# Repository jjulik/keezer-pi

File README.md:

# keezer-pi
Client/Server code for building a Keezer with a Raspberry Pi

## Complete setup guide
Download the raspbian lite image and put it on a micro SD card.

### Configure keyboard (and enable SSH)
`sudo raspi-config`

### Set the machine name
`sudo vi /etc/hosts`
`sudo vi /etc/hostname`

### Backup your wpa_supplicant
`sudo cp /etc/wpa_supplicant/wpa_supplicant.conf ~/wpa_supplicant.conf.bac`

### Connect to Wi-Fi
`wpa_passphrase "network_name" "passphrase" | sudo tee -a /etc/wpa_supplicant/wpa_supplicant.conf > /dev/null`

Then go edit the wpa_supplicant.conf to not have the password

`wpa_cli -i wlan0 reconfigure`

Check with

`ifconfig wlan0`

### Configure Wi-Fi to connect on boot
Set interface wlan0 in dhcpcd.conf

### Update Pi
`sudo apt-get update`
`sudo apt-get upgrade`

### Enable 1 wire interface
Edit /boot/config.txt

Add dtoverlay=w1-gpio

Then reboot the pi

`sudo shutdown -r -t 0`

### Install vim, git, and pip
`sudo apt-get install vim, git, pip`

### Clone the repo
`git clone https://github.com/jjulik/keezer-pi.git`

### Configure keezer-pi
Copy the keezer-pi.config.example to keezer-pi.config

Then edit the settings

### Install keezer-pi
`sudo ./install.sh`

Reboot the pi once more

`sudo shutdown -r -t 0`

And everything should be working correctly now

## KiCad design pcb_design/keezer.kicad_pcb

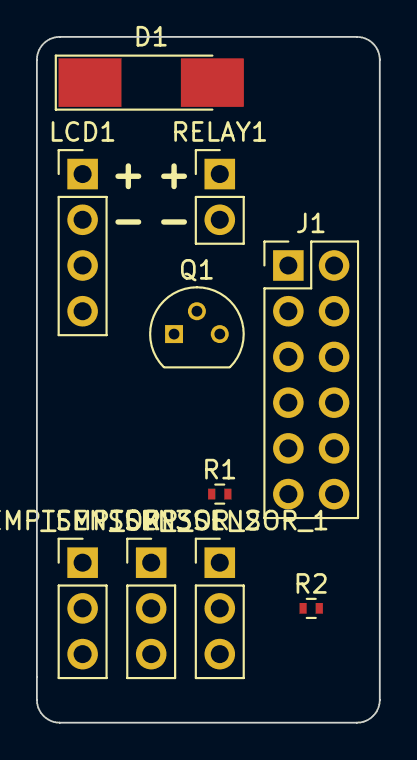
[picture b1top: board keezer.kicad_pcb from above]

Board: 2 copper layers, 19.1 x 38.1 mm, 10 parts (0 on the bottom side), 9 nets, no tracks yet.

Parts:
D1: D; D_MELF_Handsoldering
J1: CONN_02X06; Pin_Header_Straight_2x06_Pitch2.54mm
LCD1: CONN_01X04_FEMALE; Socket_Strip_Straight_1x04_Pitch2.54mm
Q1: PN2222A; TO-92_Molded_Narrow
R1: 1K; R_0402
R2: 3.9K; R_0402
RELAY1: CONN_01X02_FEMALE; Socket_Strip_Straight_1x02_Pitch2.54mm
TEMP_SENSOR_1, TEMP_SENSOR_2, TEMP_SENSOR_3: CONN_01X03_FEMALE; Socket_Strip_Straight_1x03_Pitch2.54mm

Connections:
+3V3: J1.2, R2.1, TEMP_SENSOR_1.1, TEMP_SENSOR_2.1, TEMP_SENSOR_3.1
+5V: D1.1, J1.1, LCD1.1, RELAY1.1
BCM4: J1.8, R2.2, TEMP_SENSOR_1.3, TEMP_SENSOR_2.3, TEMP_SENSOR_3.3
BCM17: J1.12, R1.1
GND: J1.10, LCD1.2, Q1.1, TEMP_SENSOR_1.2, TEMP_SENSOR_2.2, TEMP_SENSOR_3.2
RELAY_OUT: D1.2, Q1.3, RELAY1.2
SCL: J1.6, LCD1.3
SDA: J1.4, LCD1.4
TRANSISTOR_BASE: Q1.2, R1.2

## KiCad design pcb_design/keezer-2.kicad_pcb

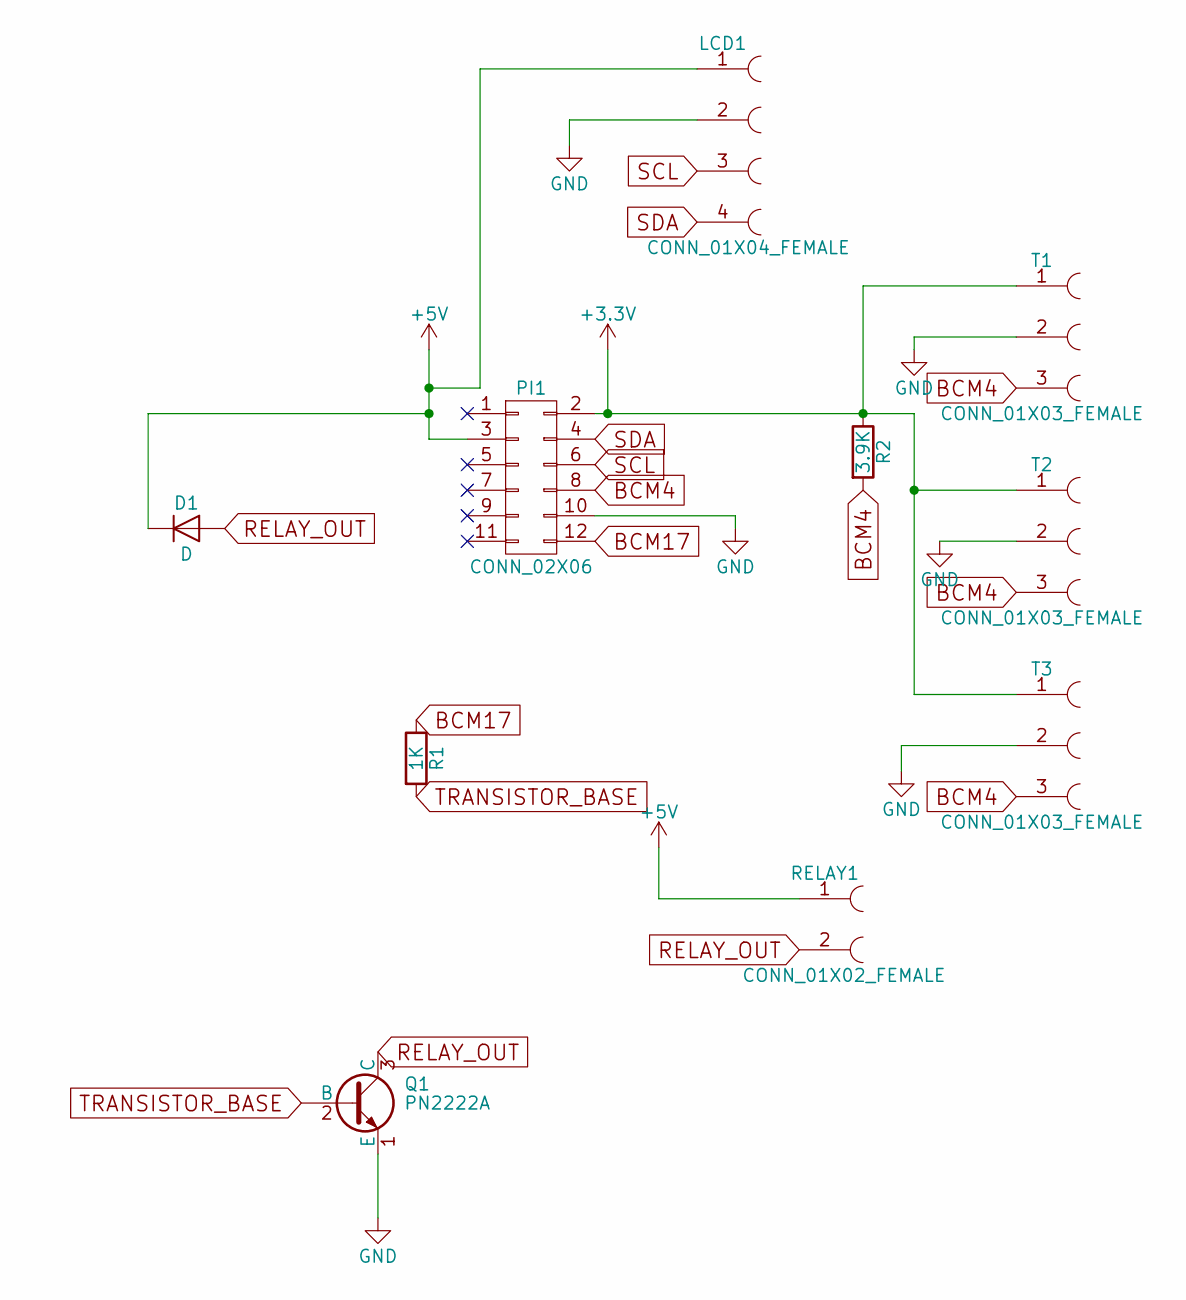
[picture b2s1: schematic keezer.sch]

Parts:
D1: D; D_DO-41_SOD81_P7.62mm_Horizontal
LCD1: CONN_01X04_FEMALE; Socket_Strip_Angled_1x04_Pitch2.54mm
PI1: CONN_02X06; Pin_Header_Straight_2x06_Pitch2.54mm
Q1: PN2222A; TO-92_Inline_Wide
R1: 1K; R_Axial_DIN0207_L6.3mm_D2.5mm_P7.62mm_Horizontal
R2: 3.9K; R_Axial_DIN0207_L6.3mm_D2.5mm_P7.62mm_Horizontal
RELAY1: CONN_01X02_FEMALE; Socket_Strip_Angled_1x02_Pitch2.54mm
T1, T2, T3: CONN_01X03_FEMALE; Socket_Strip_Angled_1x03_Pitch2.54mm

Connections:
+3V3: PI1.2, R2.1, T1.1, T2.1, T3.1
+5V: D1.1 (K), LCD1.1, PI1.3, RELAY1.1
BCM4: PI1.8, R2.2, T1.3, T2.3, T3.3
BCM17: PI1.12, R1.1
GND: LCD1.2, PI1.10, Q1.1 (E), T1.2, T2.2, T3.2
RELAY_OUT: D1.2 (A), Q1.3 (C), RELAY1.2
SCL: LCD1.3, PI1.6
SDA: LCD1.4, PI1.4
TRANSISTOR_BASE: Q1.2 (B), R1.2

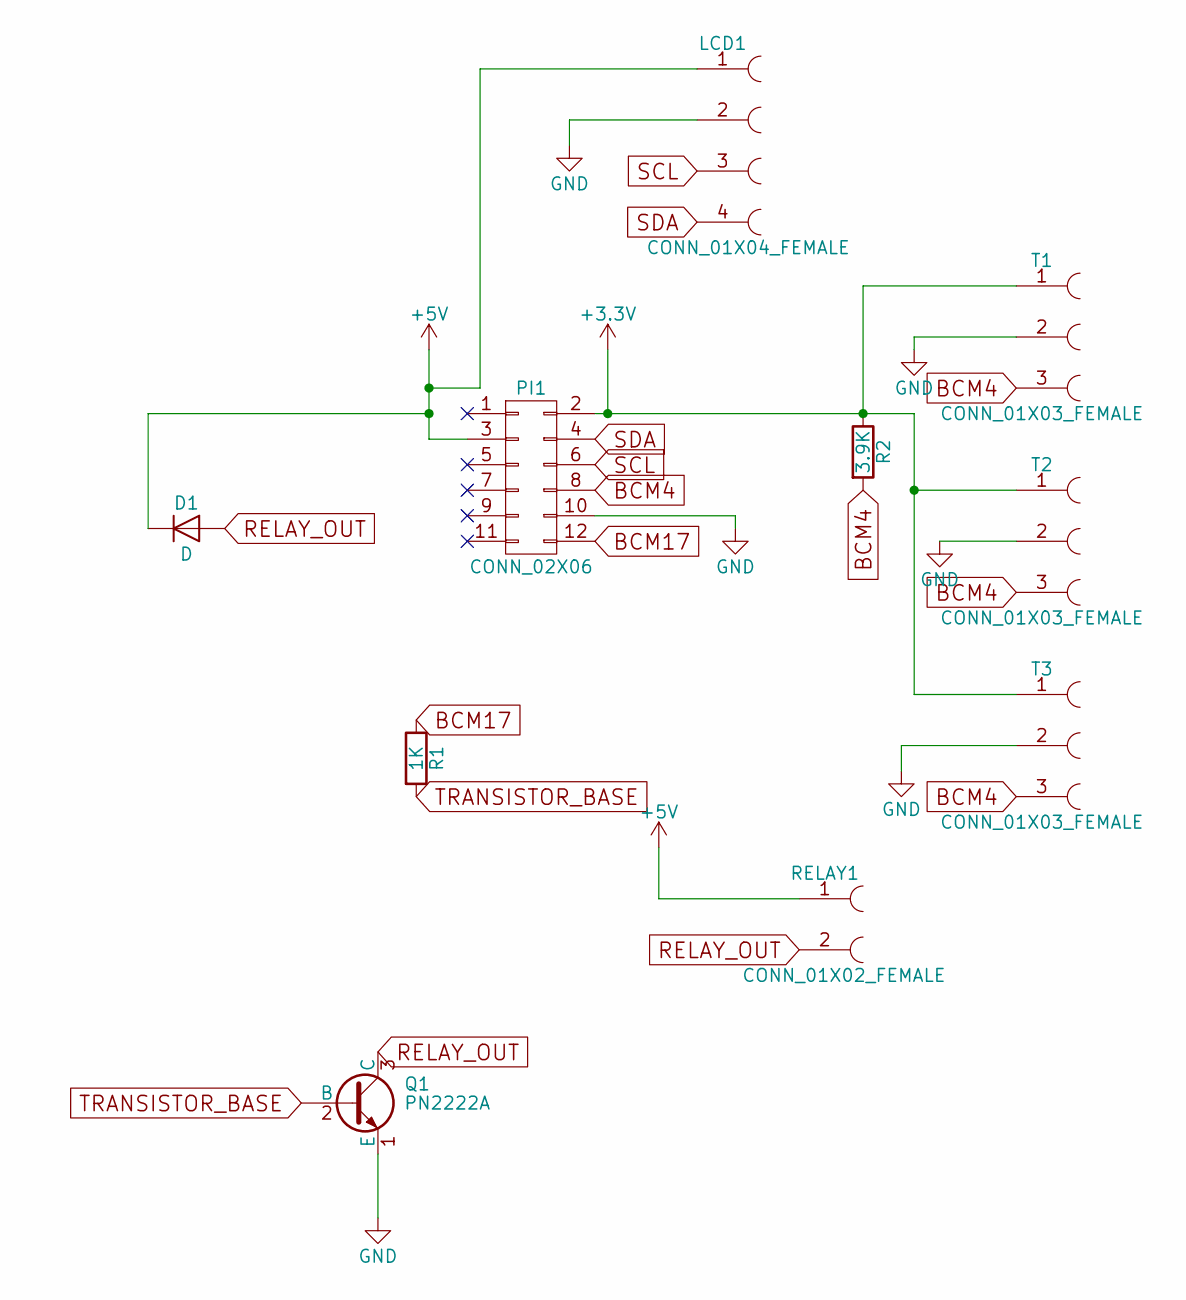
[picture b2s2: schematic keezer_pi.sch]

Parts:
D1: D; D_DO-41_SOD81_P7.62mm_Horizontal
LCD1: CONN_01X04_FEMALE; Socket_Strip_Angled_1x04_Pitch2.54mm
PI1: CONN_02X06; Pin_Header_Straight_2x06_Pitch2.54mm
Q1: PN2222A; TO-92_Inline_Wide
R1: 1K; R_Axial_DIN0207_L6.3mm_D2.5mm_P7.62mm_Horizontal
R2: 3.9K; R_Axial_DIN0207_L6.3mm_D2.5mm_P7.62mm_Horizontal
RELAY1: CONN_01X02_FEMALE; Socket_Strip_Angled_1x02_Pitch2.54mm
T1, T2, T3: CONN_01X03_FEMALE; Socket_Strip_Angled_1x03_Pitch2.54mm

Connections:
+3V3: PI1.2, R2.1, T1.1, T2.1, T3.1
+5V: D1.1 (K), LCD1.1, PI1.3, RELAY1.1
BCM4: PI1.8, R2.2, T1.3, T2.3, T3.3
BCM17: PI1.12, R1.1
GND: LCD1.2, PI1.10, Q1.1 (E), T1.2, T2.2, T3.2
RELAY_OUT: D1.2 (A), Q1.3 (C), RELAY1.2
SCL: LCD1.3, PI1.6
SDA: LCD1.4, PI1.4
TRANSISTOR_BASE: Q1.2 (B), R1.2

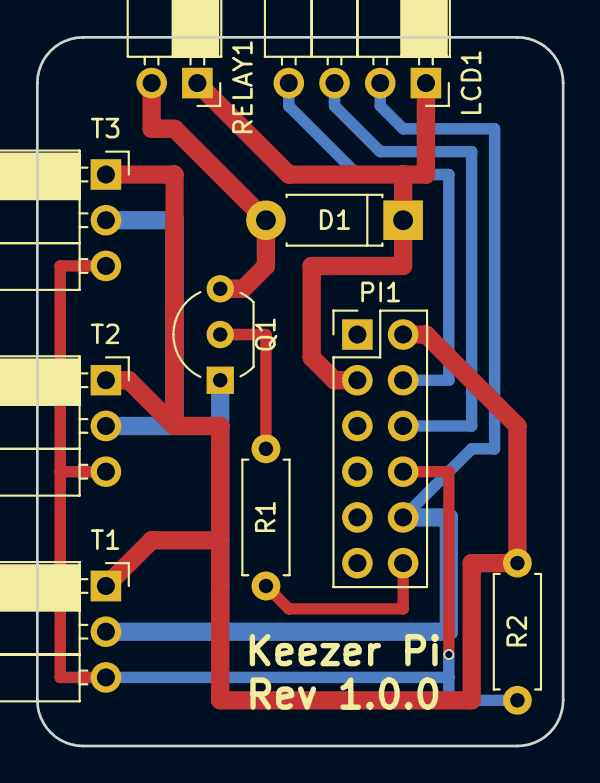
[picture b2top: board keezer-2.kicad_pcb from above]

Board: 2 copper layers, 29.2 x 39.4 mm, 10 parts (0 on the bottom side), 9 nets.

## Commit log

2017-03-27 Create license
2017-04-10 Scaffolding for flask app, db initialization
2017-04-10 Ignore sqlite databases
2017-04-10 Fix addtoken cli method
2017-04-10 CLI method for getting active tokens, fix inserts by committing them
2017-04-10 CLI commands for adding/getting sensors
2017-04-11 Add authorization decorator
2017-04-14 Fix spacing in readme
2017-04-15 Python script for testing temp sensors
2017-04-15 Add sample data from sensors
2017-04-15 Update gitignore to exclude logs, add keezer_client file
2017-04-15 Configuration for client, logging to server
2017-04-15 Add sample config
2017-04-15 Server side logging of client errors
2017-04-15 Fix sending errors to server from client
2017-04-15 Async error upload so the main thread loop doesn't get blocked
2017-04-15 Endpoint for sensor readings
2017-04-15 Log temperature readings from client and send to server
2017-04-16 Add logic for controlling fridge relay
2017-04-23 Update config example to include temp settings
2017-04-23 Fix error when no secondary sensor is attached
2017-04-23 Add pcb design files; schematics are complete, but pcb design isn't
2017-04-23 Fix some silkscreen; fill bottom layer with ground zone
2017-04-23 Add more silkscreen
2017-04-23 Update pcb design to match OSH Park's minimum requirements
2017-04-23 Wire everything up in the pcb
2017-04-23 Update pcb file names, remove duplicate files
2017-04-26 Add install script and service file for systemd, update requirements.txt
2017-04-27 Adding temperature graphs for server
2017-04-28 Send unix time from client instead of formatted time
2017-04-28 Handle unix times in charts
2017-04-29 Server side power logging
2017-04-29 Send power readings from client
2017-04-29 Different chart labels for temperature and power sensors
2017-04-29 Cleaning up power charts
2017-04-29 Constrain height of charts
2017-11-13 Install script was copying example config rather than the real one
2017-11-13 Update example config to use pin 17, which matches the pcb design
2017-11-13 Update readme with instructions on how to setup keezer-pi from scratch
